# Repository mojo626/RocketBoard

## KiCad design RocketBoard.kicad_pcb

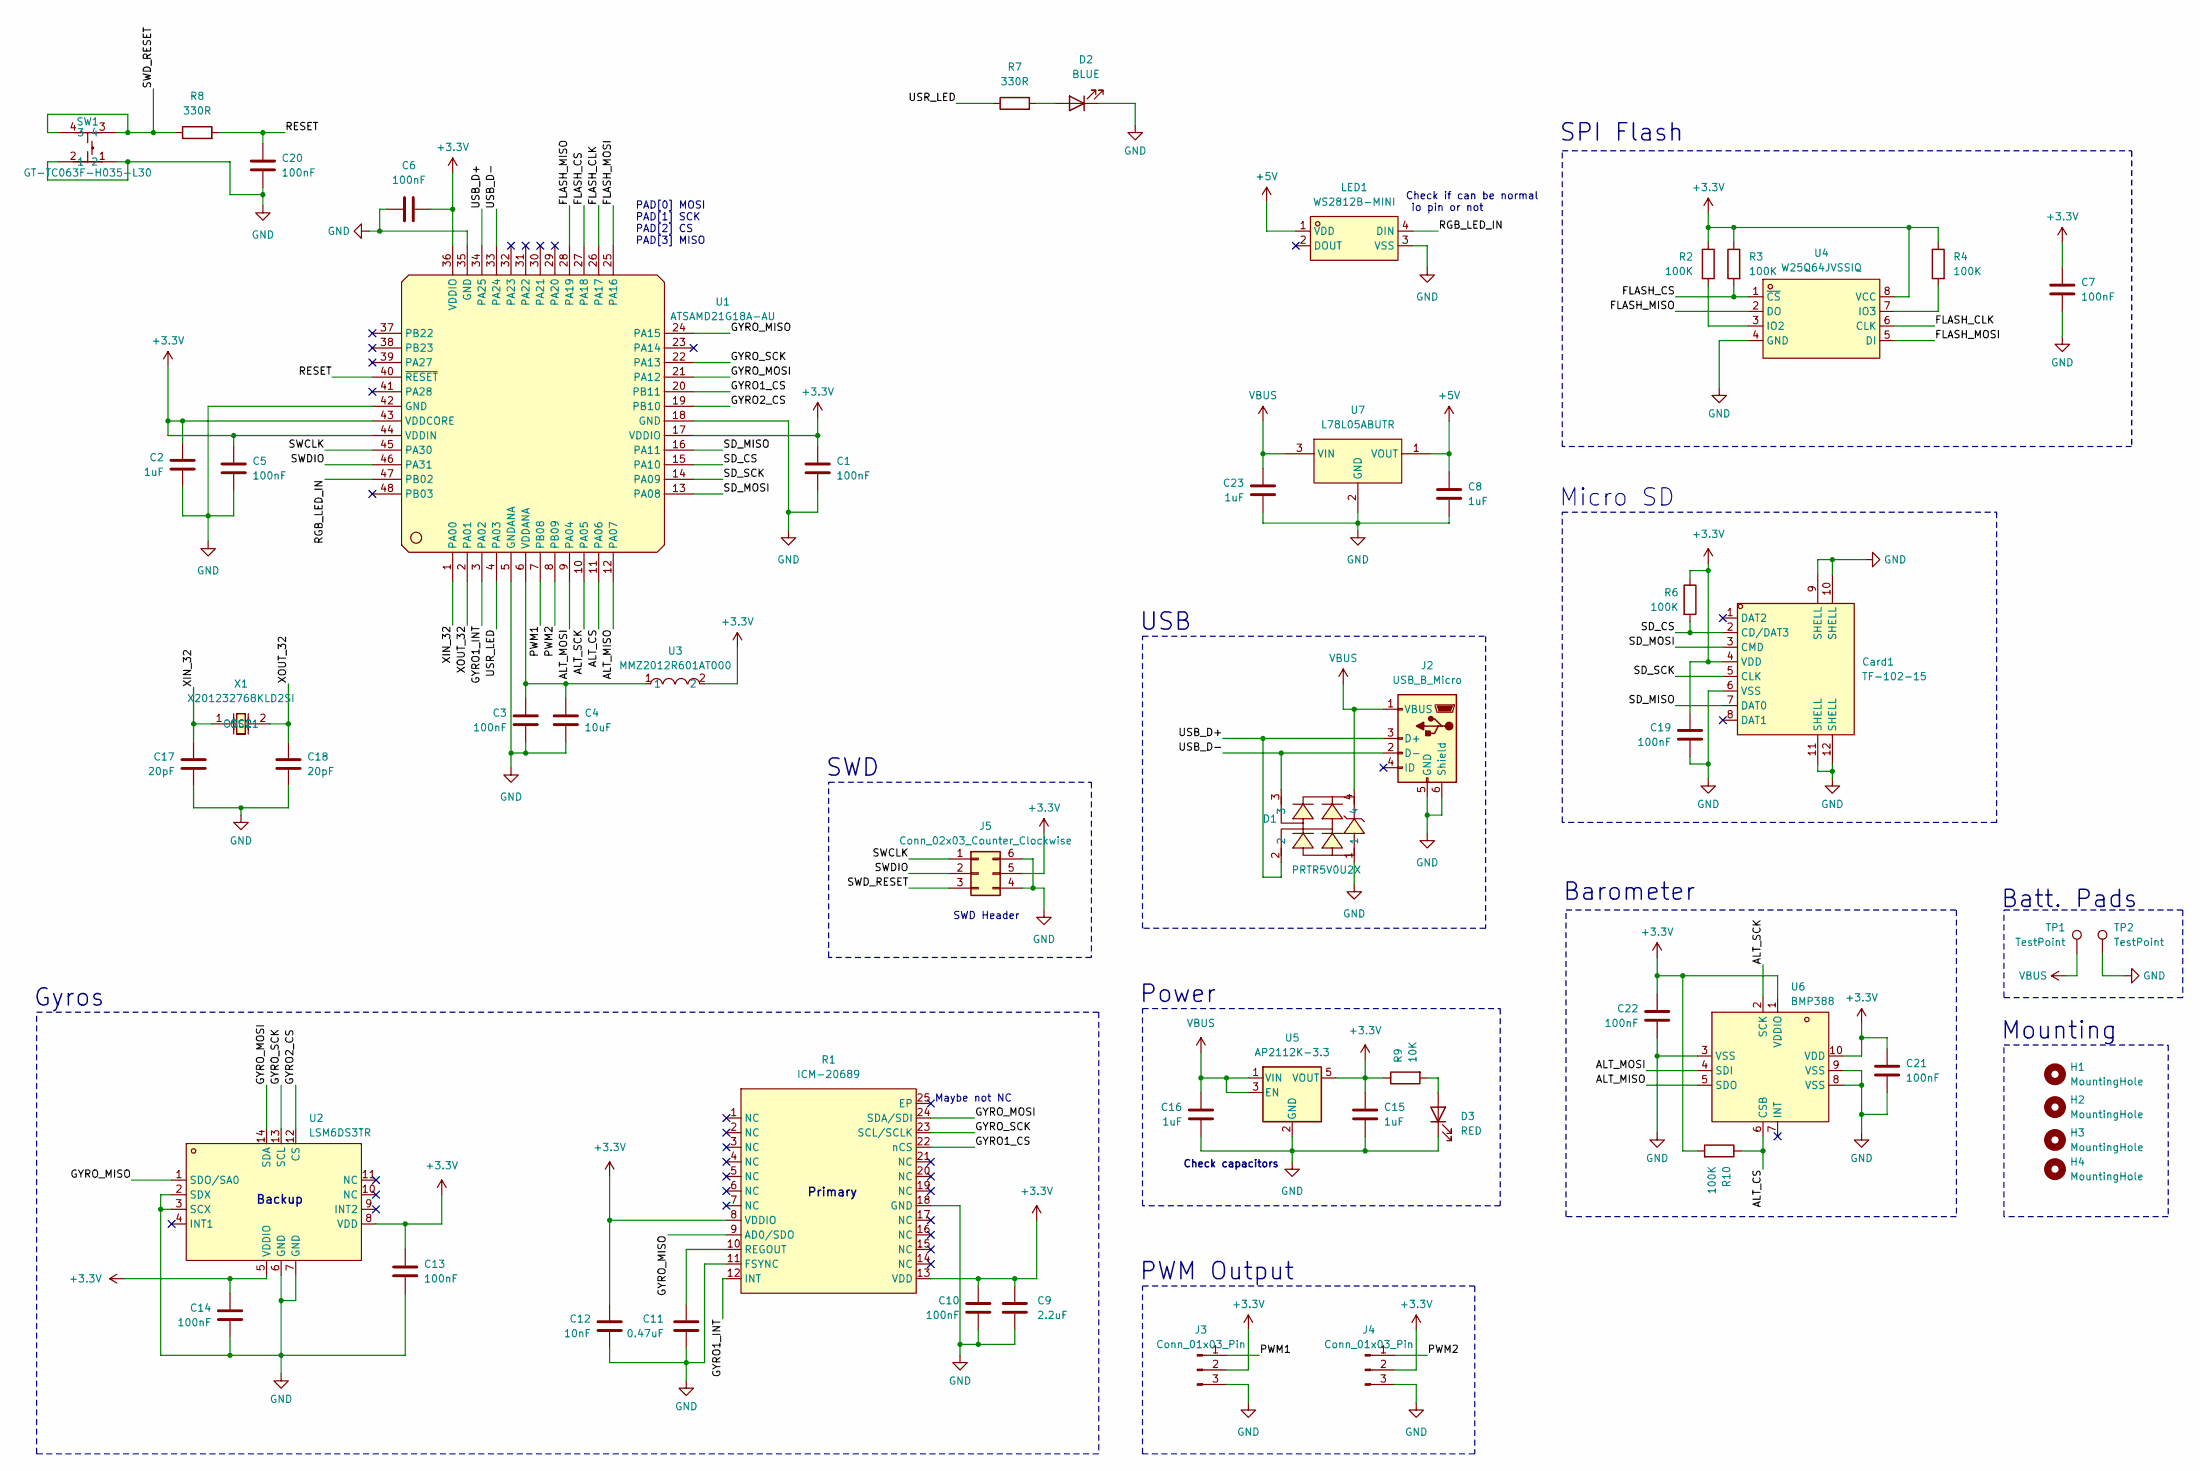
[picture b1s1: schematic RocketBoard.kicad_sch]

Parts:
C1, C3, C5, C6, C7, C10, C13, C14, C19, C20, C21, C22: 100nF; C_0603_1608Metric
C2, C8, C15, C16, C23: 1uF; C_0402_1005Metric
C4: 10uF; C_0603_1608Metric
C9: 2.2uF; C_0603_1608Metric
C11: 0.47uF; C_0603_1608Metric
C12: 10nF; C_0402_1005Metric
C17, C18: 20pF; C_0603_1608Metric
Card1: TF-102-15; TF-SMD_TF-102-15; LCSC Part C266609
D1: PRTR5V0U2X; SOT-143-4_L2.9-W1.3-P1.92-LS2.4-BL; LCSC Part C2827688
D2: BLUE; LED_0402_1005Metric
D3: RED; LED_0402_1005Metric
H1, H2, H3, H4: MountingHole; MountingHole_3mm
J2: USB_B_Micro; USB_Micro-B_Amphenol_10103594-0001LF_Horizontal
J3, J4: Conn_01x03_Pin; PinHeader_1x03_P2.54mm_Vertical
J5: Conn_02x03_Counter_Clockwise; PinHeader_2x03_P2.54mm_Vertical
LED1: WS2812B-MINI; LED-SMD_4P-L3.5-W3.5-TL_WS2812B; LCSC Part C527089
R1: ICM-20689; QFN-24_L4.0-W4.0-P0.50-TL-EP2.6; LCSC Part C2649494
R2, R3, R4, R6, R10: 100K; R_0603_1608Metric
R7, R8: 330R; R_0603_1608Metric
R9: 10K; R_0603_1608Metric
SW1: GT-TC063F-H035-L30; SW-SMD_4P-L6.2-W6.2-P4.00-LS7.2; LCSC Part C963195
TP1, TP2: TestPoint; TestPoint_Pad_3.0x3.0mm
U1: ATSAMD21G18A-AU; TQFP-48_L7.0-W7.0-P0.50-LS9.0-BL; LCSC Part C78624
U2: LSM6DS3TR; LGA-14_L3.0-W2.5-P0.50-TL; LCSC Part C95230
U3: MMZ2012R601AT000; L0805; LCSC Part C275467
U4: W25Q64JVSSIQ; SOP-8_L5.3-W5.3-P1.27-LS8.0-BL; LCSC Part C83140
U5: AP2112K-3.3; SOT-23-5
U6: BMP388; SENSORM-SMD_BMP388; LCSC Part C779278
U7: L78L05ABUTR; SOT-89-3_L4.5-W2.5-P1.50-LS4.2-TL; LCSC Part C42738
X1: X201232768KLD2SI; OSC-SMD_L2.0-W1.2; LCSC Part C383842

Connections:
+3.3V: C1.1, C2.1, C5.1, C6.2, C7.1, C9.1, C10.1, C12.1, C13.1, C14.1, C15.1, C19.1, C21.1, C22.1, Card1.4 (VDD), J3.2, J4.2, J5.5, R1.8 (VDDIO), R1.13 (VDD), R2.1, R3.1, R4.1, R6.1, R9.1, R10.2, U1.17 (VDDIO), U1.36 (VDDIO), U1.43 (VDDCORE), U1.44 (VDDIN), U2.5 (VDDIO), U2.8 (VDD), U3.2, U4.8 (VCC), U5.5 (VOUT), U6.1 (VDDIO), U6.10 (VDD)
+5V: C8.1, LED1.1 (VDD), U7.1 (VOUT)
/ALT_CS: R10.1, U1.11 (PA06), U6.6 (CSB)
/ALT_MISO: U1.12 (PA07), U6.5 (SDO)
/ALT_MOSI: U1.9 (PA04), U6.4 (SDI)
/ALT_SCK: U1.10 (PA05), U6.2 (SCK)
/FLASH_CLK: U1.26 (PA17), U4.6 (CLK)
/FLASH_CS: R3.2, U1.27 (PA18), U4.1 (~CS)
/FLASH_MISO: U1.28 (PA19), U4.2 (DO)
/FLASH_MOSI: U1.25 (PA16), U4.5 (DI)
/GYRO1_CS: R1.22 (nCS), U1.20 (PB11)
/GYRO1_INT: R1.12 (INT), U1.3 (PA02)
/GYRO2_CS: U1.19 (PB10), U2.12 (CS)
/GYRO_MISO: R1.9 (AD0/SDO), U1.24 (PA15), U2.1 (SDO/SA0)
/GYRO_MOSI: R1.24 (SDA/SDI), U1.21 (PA12), U2.14 (SDA)
/GYRO_SCK: R1.23 (SCL/SCLK), U1.22 (PA13), U2.13 (SCL)
/PWM1: J3.1, U1.7 (PB08)
/PWM2: J4.1, U1.8 (PB09)
/RESET: C20.1, R8.2, U1.40 (~RESET)
/RGB_LED_IN: LED1.4 (DIN), U1.47 (PB02)
/SD_CS: Card1.2 (CD/DAT3), R6.2, U1.15 (PA10)
/SD_MISO: Card1.7 (DAT0), U1.16 (PA11)
/SD_MOSI: Card1.3 (CMD), U1.13 (PA08)
/SD_SCK: Card1.5 (CLK), U1.14 (PA09)
/SWCLK: J5.1, U1.45 (PA30)
/SWDIO: J5.2, U1.46 (PA31)
/SWD_RESET: J5.3, R8.1, SW1.3, SW1.4
/USB_D+: D1.2, J2.3 (D+), U1.34 (PA25)
/USB_D-: D1.3, J2.2 (D-), U1.33 (PA24)
/USR_LED: R7.1, U1.4 (PA03)
/XIN_32: C17.1, U1.1 (PA00), X1.1 (OSC1)
/XOUT_32: C18.1, U1.2 (PA01), X1.2 (OSC2)
GND: C1.2, C2.2, C3.2, C4.2, C5.2, C6.1, C7.2, C8.2, C9.2, C10.2, C11.2, C12.2, C13.2, C14.2, C15.2, C16.2, C17.2, C18.2, C19.2, C20.2, C21.2, C22.2, C23.2, Card1.6 (VSS), Card1.9 (SHELL), Card1.10 (SHELL), Card1.11 (SHELL), Card1.12 (SHELL), D1.1, D2.1 (K), D3.1 (K), J2.5 (GND), J2.6 (Shield), J3.3, J4.3, J5.4, J5.6, LED1.3 (VSS), R1.11 (FSYNC), R1.18 (GND), SW1.1, SW1.2, TP2.1, U1.5 (GNDANA), U1.18 (GND), U1.35 (GND), U1.42 (GND), U2.2 (SDX), U2.3 (SCX), U2.6 (GND), U2.7 (GND), U4.4 (GND), U5.2 (GND), U6.3 (VSS), U6.8 (VSS), U6.9 (VSS), U7.2 (GND)
unnamed: D2.2 (A), R7.2
unnamed: D3.2 (A), R9.2
unnamed: C11.1, R1.10 (REGOUT)
unnamed: C3.1, C4.1, U1.6 (VDDANA), U3.1
unnamed: R2.2, U4.3 (IO2)
unnamed: R4.2, U4.7 (IO3)
VBUS: C16.1, C23.1, D1.4, J2.1 (VBUS), TP1.1, U5.1 (VIN), U5.3 (EN), U7.3 (VIN)

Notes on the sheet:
Primary
PWM Output
Micro SD
Mounting
Backup
Check capacitors
Maybe not NC
PAD[0] MOSI PAD[1] SCK PAD[2] CS PAD[3] MISO
SWD Header
Check if can be normal io pin or not
Batt. Pads
SPI Flash
Gyros
Barometer
SWD
Power
USB

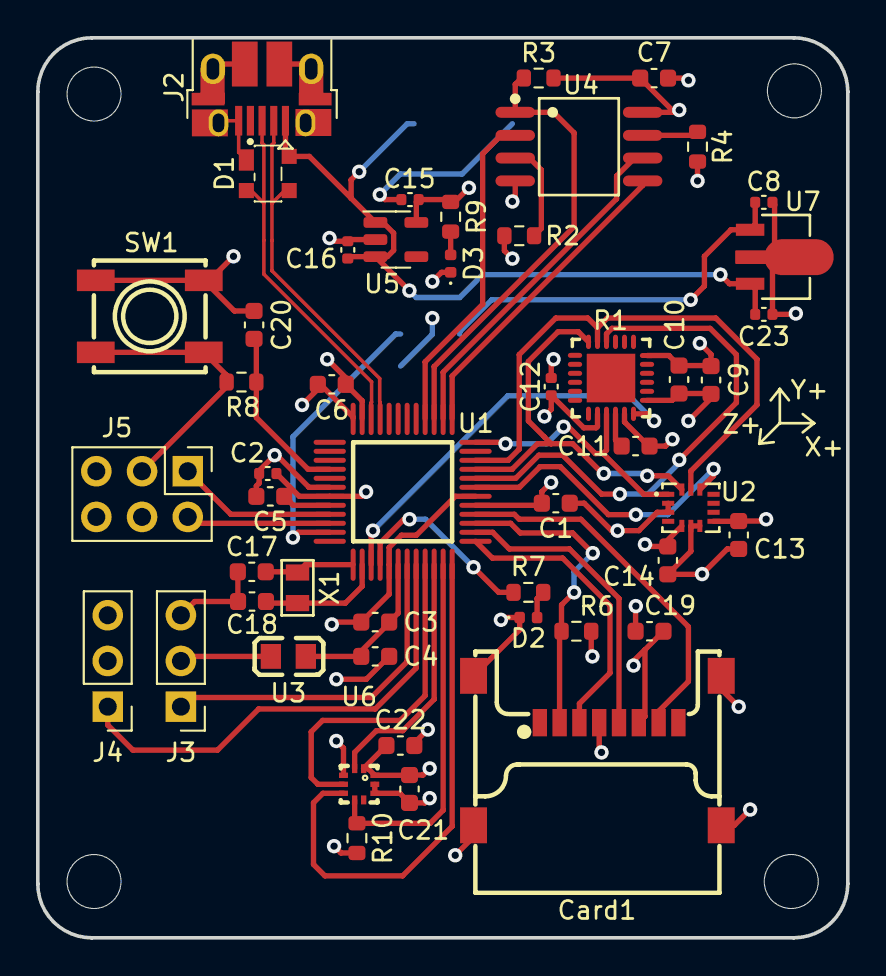
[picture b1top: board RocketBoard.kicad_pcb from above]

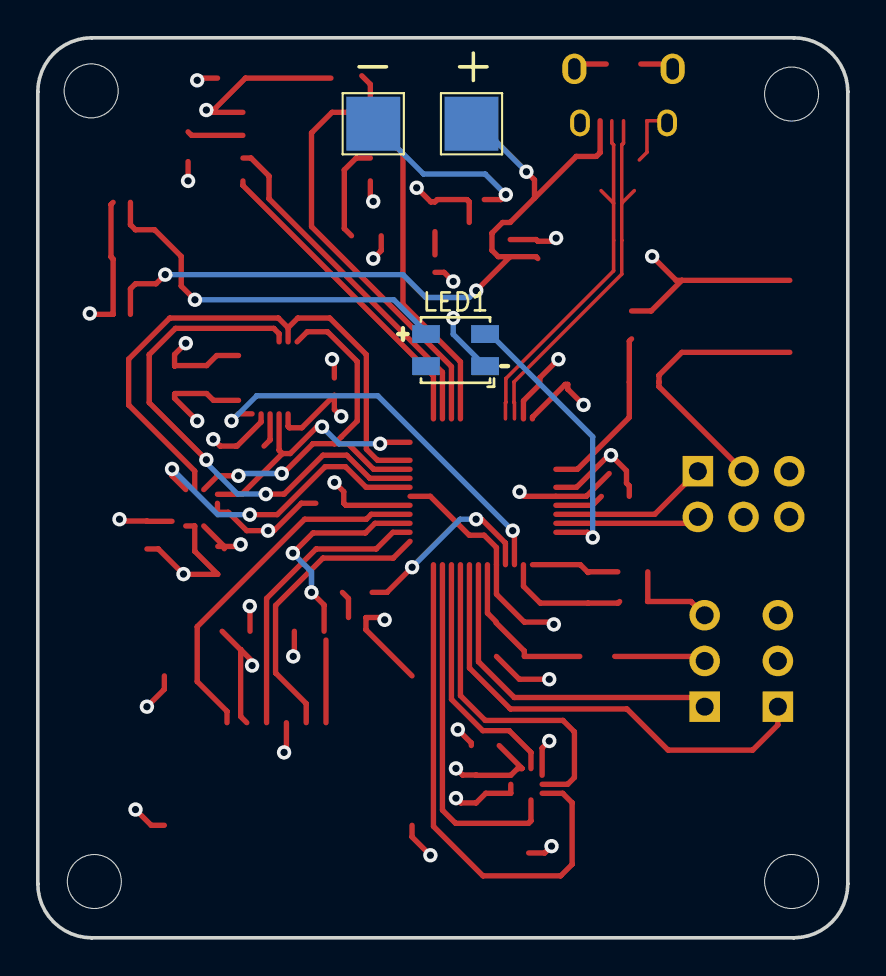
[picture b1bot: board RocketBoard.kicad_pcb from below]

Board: 4 copper layers, 45.0 x 50.0 mm, 56 parts (3 on the bottom side), 40 nets.

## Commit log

2024-06-11 adding files
2024-06-11 routing start
2024-06-11 started placing things
2024-06-12 routed?
